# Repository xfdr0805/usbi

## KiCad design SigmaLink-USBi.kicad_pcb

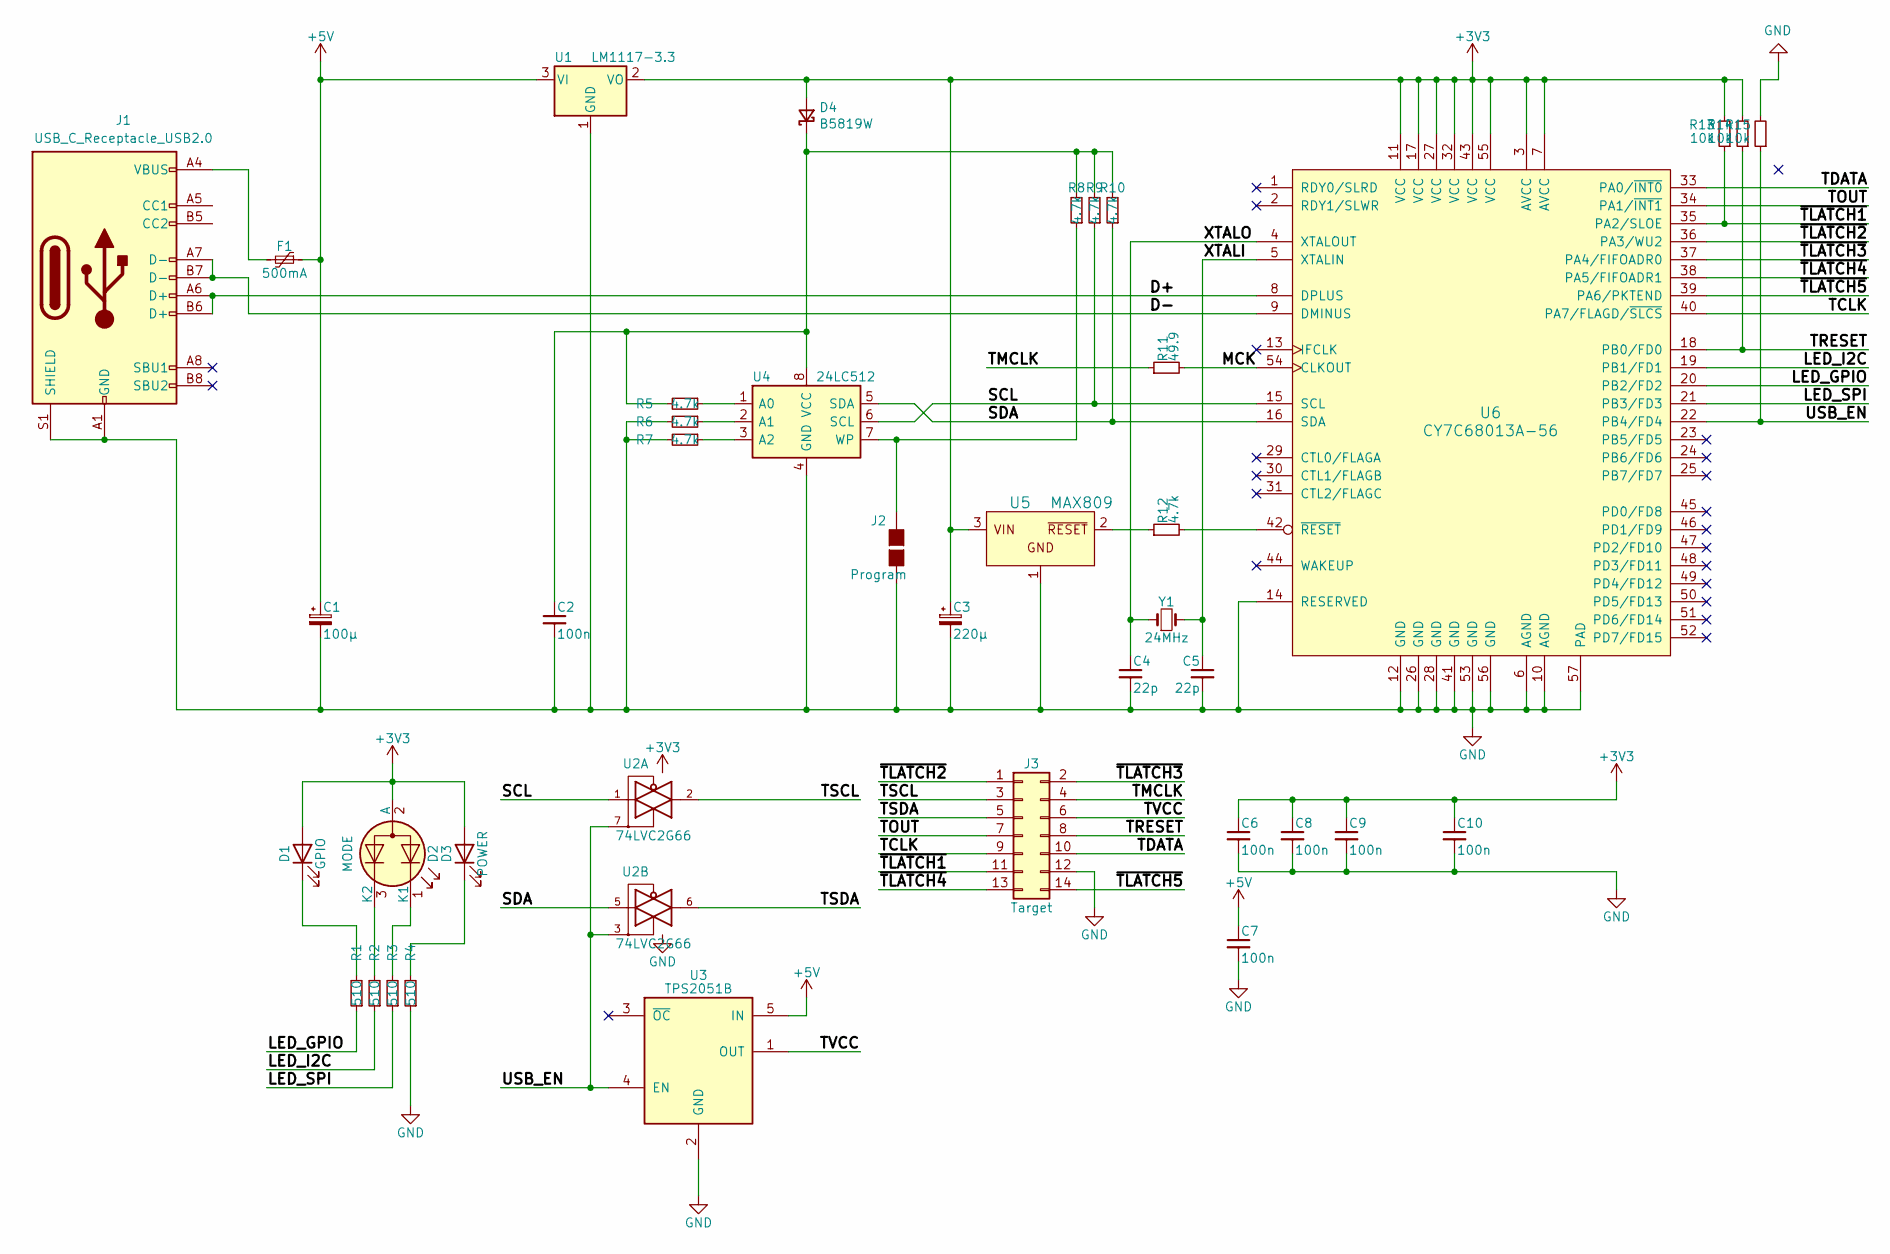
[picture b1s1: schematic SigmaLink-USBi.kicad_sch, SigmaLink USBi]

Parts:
C1: 100µ; CP_Elec_6.3x5.3
C2, C6, C7, C8, C9, C10: 100n; C_0603_1608Metric
C3: 220µ; CP_Elec_6.3x5.3
C4, C5: 22p; C_0603_1608Metric
D1: GPIO; LED_D3.0mm
D2: MODE; LED_D3.0mm-3
D3: POWER; LED_D3.0mm
D4: B5819W; D_SOD-123
F1: 500mA; Fuse_1812_4532Metric_Pad1.30x3.40mm_HandSolder
J1: USB_C_Receptacle_USB2.0; USB_C_Receptacle_XKB_U262-16XN-4BVC11
J2: Program; PinHeader_1x02_P1.27mm_Vertical
J3: Target; IDC-Header_2x07_P2.54mm_Horizontal
R1, R2, R3, R4: 510; R_0603_1608Metric
R5, R6, R7, R8, R9, R10, R12: 4.7k; R_0603_1608Metric
R11: 49.9; R_0603_1608Metric
R13, R14, R15: 10k; R_0603_1608Metric
U1: LM1117-3.3; SOT-223-3_TabPin2
U2: 74LVC2G66; VSSOP-8_3.0x3.0mm_P0.65mm
U3: TPS2051B; SOT-23-5
U4: 24LC512; SOIC-8_3.9x4.9mm_P1.27mm
U5: MAX809; SOT-23
U6: CY7C68013A-56; QFN-56-1EP_8x8mm_P0.5mm_EP4.5x5.2mm_ThermalVias
Y1: 24MHz; Crystal_SMD_5032-2Pin_5.0x3.2mm

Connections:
+3V3: C3.1, C6.1, C8.1, C9.1, C10.1, D1.2 (A), D2.2 (A), D3.2 (A), D4.2 (A), R13.2, R14.2, U1.2 (VO), U2.8 (VCC), U5.3 (VIN), U6.3 (AVCC), U6.7 (AVCC), U6.11 (VCC), U6.17 (VCC), U6.27 (VCC), U6.32 (VCC), U6.43 (VCC), U6.55 (VCC)
+5V: C1.1, C7.1, F1.1, U1.3 (VI), U3.5 (IN)
/D+: J1.A6 (D+), J1.B6 (D+), U6.8 (DPLUS)
/D-: J1.A7 (D-), J1.B7 (D-), U6.9 (DMINUS)
/LED_GPIO: R1.1, U6.20 (PB2/FD2)
/LED_I2C: R2.1, U6.19 (PB1/FD1)
/LED_SPI: R3.1, U6.21 (PB3/FD3)
/MCK: R11.2, U6.54 (CLKOUT)
/SCL: R9.1, U2.1, U4.6 (SCL), U6.15 (SCL)
/SDA: R10.1, U2.5, U4.5 (SDA), U6.16 (SDA)
/TCLK: J3.9, U6.40 (PA7/FLAGD/~SLCS)
/TDATA: J3.10, U6.33 (PA0/~INT0)
/TMCLK: J3.4, R11.1
/TOUT: J3.7, U6.34 (PA1/~INT1)
/TRESET: J3.8, R14.1, U6.18 (PB0/FD0)
/TSCL: J3.3, U2.2
/TSDA: J3.5, U2.6
/TVCC: J3.6, U3.1 (OUT)
/USB_EN: R15.1, U2.3, U2.7, U3.4 (EN), U6.22 (PB4/FD4)
/XTALI: C5.1, U6.5 (XTALIN), Y1.2
/XTALO: C4.1, U6.4 (XTALOUT), Y1.1
/~TLATCH1: J3.11, R13.1, U6.35 (PA2/SLOE)
/~TLATCH2: J3.1, U6.36 (PA3/WU2)
/~TLATCH3: J3.2, U6.37 (PA4/FIFOADR0)
/~TLATCH4: J3.13, U6.38 (PA5/FIFOADR1)
/~TLATCH5: J3.14, U6.39 (PA6/PKTEND)
GND: C1.2, C2.2, C3.2, C4.2, C5.2, C6.2, C7.2, C8.2, C9.2, C10.2, J1.A1 (GND), J1.A12 (GND), J1.B1 (GND), J1.B12 (GND), J1.S1 (SHIELD), J2.2 (G2), J3.12, R4.1, R6.2, R7.2, R15.2, U1.1 (GND), U2.4 (GND), U3.2 (GND), U4.4 (GND), U5.1 (GND), U6.6 (AGND), U6.10 (AGND), U6.12 (GND), U6.14 (RESERVED), U6.26 (GND), U6.28 (GND), U6.41 (GND), U6.53 (GND), U6.56 (GND), U6.57 (PAD)
unnamed: C2.1, D4.1 (K), R5.2, R8.2, R9.2, R10.2, U4.8 (VCC)
unnamed: D1.1 (K), R1.2
unnamed: D2.1 (K1), R3.2
unnamed: D2.3 (K2), R2.2
unnamed: D3.1 (K), R4.2
unnamed: F1.2, J1.A4 (VBUS), J1.A9 (VBUS), J1.B4 (VBUS), J1.B9 (VBUS)
unnamed: J2.1 (G1), R8.1, U4.7 (WP)
unnamed: R5.1, U4.1 (A0)
unnamed: R6.1, U4.2 (A1)
unnamed: R7.1, U4.3 (A2)
unnamed: R12.1, U5.2 (~RESET)
unnamed: R12.2, U6.42 (~RESET)

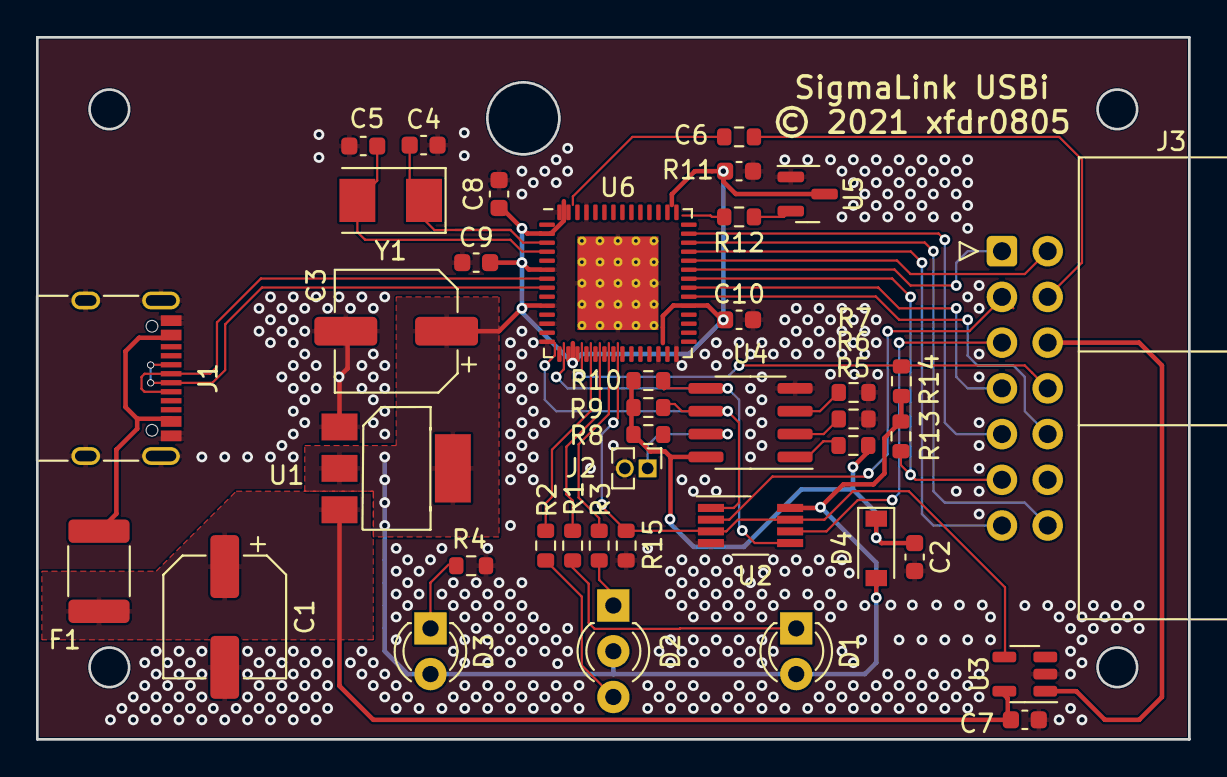
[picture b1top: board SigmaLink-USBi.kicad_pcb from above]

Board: 2 copper layers, 64.0 x 39.0 mm, 40 parts (0 on the bottom side), 39 nets.

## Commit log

2021-04-19 修改排阻为容易找到的材料 修改USB接口为TYPEC
2021-04-21 修改丝印

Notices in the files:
SigmaLink-USBi.kicad_pcb:
© 2021 xfdr0805
